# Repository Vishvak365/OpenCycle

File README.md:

# OpenCycle

An open-source GPS bike computer you print, solder and own.

- **Screen:** 2.4" IPS TFT, 240 × 320, 1200 nit (Newhaven, ST7789), auto-dimmed by an ambient-light sensor.
- **Radios:** ESP32-S3 (Wi-Fi, Bluetooth to the phone, native USB) + Ezurio BL652 for ANT+ and Bluetooth sensors + u-blox MAX-M10S GPS with a 12 mm ceramic patch.
- **Also:** BMP581 barometer, I²S amp and sealed speaker, 3 soft keys + 2 side buttons, USB-C charging.
- **Battery:** 1200 mAh LiPo, ~10–22 h riding (estimate, not measured).
- **Case:** 52 × 92.4 × 17 mm, FDM-printed, Garmin quarter-turn mount; standard, aero and rugged shells.
- **Parts:** ~$89 per unit, every part priced and linked (Mouser + Digi-Key).

Everything is generated from source: the enclosure (CadQuery), the board **and** its schematic (KiCad 7 through Python + Freerouting), the BOMs, the print files and the 3D viewer.

## Status (v0.2)

| Area | State |
|---|---|
| Enclosure | Done. Fit-checked against placeholders and against every real part on the routed board. Print-ready STLs in [`print/`](print/README.md). |
| PCB | Routed, 4 layers. **DRC 0 errors / 0 unconnected**, ERC 0 errors, schematic netlist = board netlist. Gerbers, BOM and CPL in [`pcb/fab/`](pcb/fab). |
| Parts | Complete BOM with prices, links and specs: [`docs/sourcing/bom-v0.2.md`](docs/sourcing/bom-v0.2.md). |
| UI | "Lucent" design language, 10 screens: [`docs/UI.md`](docs/UI.md). |
| Firmware | Not started. The owner is finishing the UI first. Plan: [`docs/FIRMWARE.md`](docs/FIRMWARE.md). |

> **Ready to order a first prototype run, not yet built.** Nothing has been soldered or powered up. Treat the first five boards as prototypes and read the "not verified" list in [`pcb/README.md`](pcb/README.md) (RF, battery lead polarity, JLCPCB part rotations) before you pay.

## Build one

Step-by-step guides are in [`instructions/`](instructions/README.md):

1. [Order the parts](instructions/01-order-parts.md)
2. [Order the PCBs](instructions/02-order-pcb.md)
3. [Print the case](instructions/03-print-case.md)
4. [Assemble the board](instructions/04-assemble-board.md)
5. [Bring it up](instructions/05-bring-up.md)
6. [Final assembly](instructions/06-final-assembly.md)
7. [Next steps](instructions/07-next-steps.md)

## The board

A time-lapse of the board being generated (placement, fan-out, routing, pours) is in [`docs/media/pcb_timelapse.mp4`](docs/media/pcb_timelapse.mp4).

## The interface

## What's here

| Path | What it is |
|---|---|
| `cad/` | Parametric enclosure (CadQuery). `params.py` holds every dimension; `check_fit.py` and `board_fit.py` check it. |
| `pcb/` | `design.py` (parts, nets, placement, rules) → board, schematic, fab files. Status in `pcb/README.md`. |
| `print/` | Print-oriented STLs, STEP files and the cover-lens outline. |
| `viewer/` | three.js pages: `index.html` (studio viewer with net explorer) and `product.html` (product page). The Lucent reference renderer is `viewer/ui/screens_color.js`. |
| `instructions/` | How to order, build and bring up a unit. |
| `docs/` | Hardware, PCB, CAD, UI, sourcing and decision docs. Start with [`docs/README.md`](docs/README.md). |
| `tools/` | `build_all.sh` rebuilds everything; exporters for meshes, print files, BOM and the time-lapse. |
| `AGENTS.md` | Where the truth lives and what not to break, for AI agents and new contributors. |

## Quick start

```bash
# view the product (the generated assets are committed)
python3 -m http.server -d viewer 8000     # open http://localhost:8000/product.html or /index.html

# rebuild everything (CadQuery, KiCad 7, Java for Freerouting; see docs/SETUP.md)
./tools/build_all.sh
```

## Licence

No licence file has been chosen yet; until one is added, all rights are reserved by the author. The Inter typeface in `viewer/ui/fonts/` is used under the SIL Open Font License (`OFL-Inter.txt`).

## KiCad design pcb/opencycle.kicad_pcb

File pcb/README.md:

# OpenCycle main board v0.2 — status

**Ready to order a first prototype run** (5 boards): routed, DRC clean, schematic generated and netlist-matched, parts sourced, fab files exported. **Not yet built or tested** — treat the first run as a prototype and follow [`../instructions/05-bring-up.md`](../instructions/05-bring-up.md).

| What | Where |
|---|---|
| Board | `opencycle.kicad_pcb` (+ `.kicad_pro`, `.kicad_dru`, `fp-lib-table`, `sym-lib-table`: opens in KiCad 7+) |
| Schematic | `opencycle.kicad_sch`, PDF in `fab/opencycle_schematic.pdf` |
| Gerbers + drill | `fab/opencycle_v0.2_gerbers.zip` (upload to JLCPCB as-is) |
| Assembly | `fab/bom_jlcpcb.csv`, `fab/cpl_jlcpcb.csv`, `fab/assembly_front.pdf`, `fab/assembly_back.pdf` |
| Order list | `fab/bom_distributors.csv` and [`../docs/sourcing/bom-v0.2.md`](../docs/sourcing/bom-v0.2.md) |
| Checks | `drc_report.txt`, `erc_report.txt`, `check_place.py`, `check_netlist.py`, `../cad/board_fit.py` |

Everything is generated from `design.py` — do not hand-edit the board and then regenerate, you will lose the edit. If you do route by hand in KiCad, stop using the pipeline for that board and say so in `docs/DECISIONS.md`.

## Verified

- Pinouts of every IC/module against the manufacturer datasheet (see the header of `design.py` for the list and `docs/sourcing/part-specs.md` for details). Two errors in earlier notes were found and fixed: the BMP581 pin order and MAX-M10S pin 15.
- Land patterns drawn from datasheet drawings for the BMP581 and the Taoglas 12 mm patch; all other footprints from the KiCad 7 library.
- Mechanical fit of every real part (datasheet heights) against the enclosure, display, folded FFC, battery and speaker.
- DRC 0 errors / 0 unconnected; ERC 0 errors; schematic netlist == board netlist.

## Not verified (look at these before ordering / during bring-up)

1. **RF performance** of all three antennas (GPS patch ground is 46 mm wide and cut by the radio keep-outs; Taoglas characterised it on 50 × 50 mm). Expect to tune firmware (GPS LNA gain) and possibly move to a pin-fed patch later.
2. **Battery polarity** of the Adafruit lead vs. J2 (pin 1 −, pin 2 +). Q2 blocks a reversed cell, but measure before plugging in.
3. **JLCPCB rotation offsets** in `cpl_jlcpcb.csv` — JLC's preview shows each part; fix any that are rotated (common for SOT-23, QFN and connectors) in their tool before paying.
4. **RF_IN impedance**: 0.2 mm on the 1.0 mm JLC04101H-3313 stack-up is close to 50 Ω; confirm with the JLC impedance calculator or ask for impedance control.
5. **Backlight brightness** with 33 Ω ballasts: ≤ 45 mA per LED in the worst case (4.2 V, Vf 2.7 V), ~21 mA typical, so full brightness is only reached on a full battery. Don't lower the ballasts unless firmware caps the PWM duty from VBAT_SENSE: at 22 Ω the worst case is 68 mA per LED, above the 50 mA per-LED limit.
6. **Charging while running:** there is no USB power path — the system always runs from VBAT and the MCP73831 charges the cell and feeds the load in parallel (the same approach as Adafruit Feather boards). While the device is on and plugged in, the charger may not terminate (it holds 4.20 V). Fine for a few hours of charging; a power-path charger (e.g. BQ24072) is the v0.3 upgrade if this matters.
7. **Firmware**: nothing is written yet; the pin map is in `docs/HARDWARE.md`.

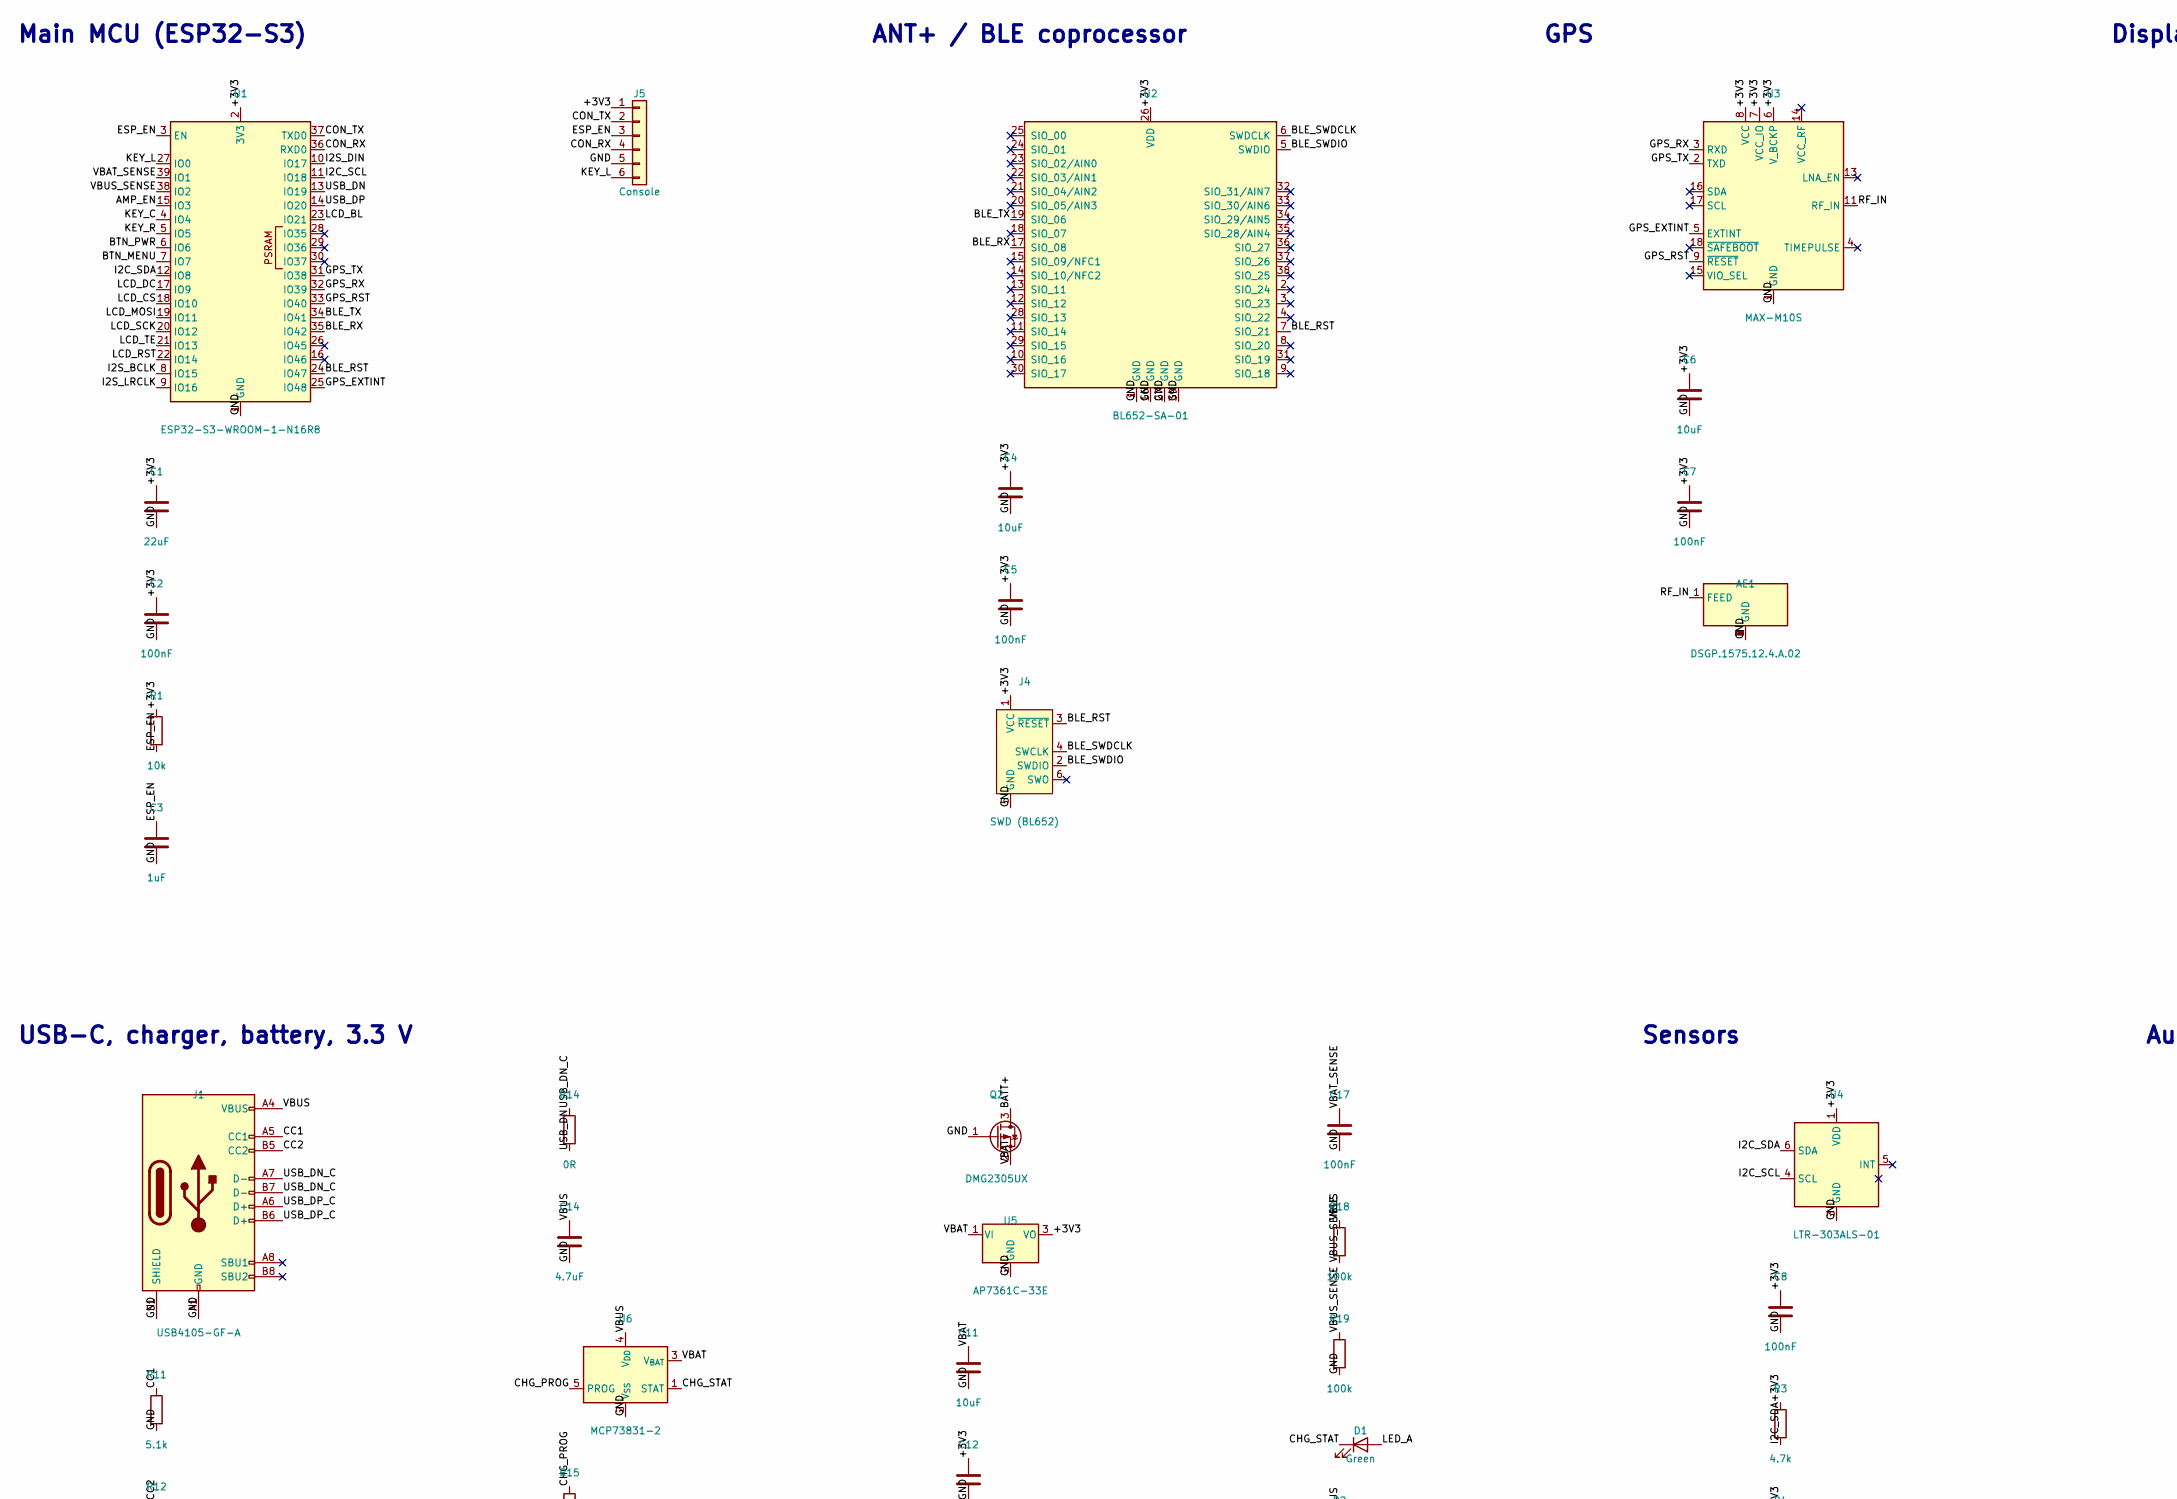
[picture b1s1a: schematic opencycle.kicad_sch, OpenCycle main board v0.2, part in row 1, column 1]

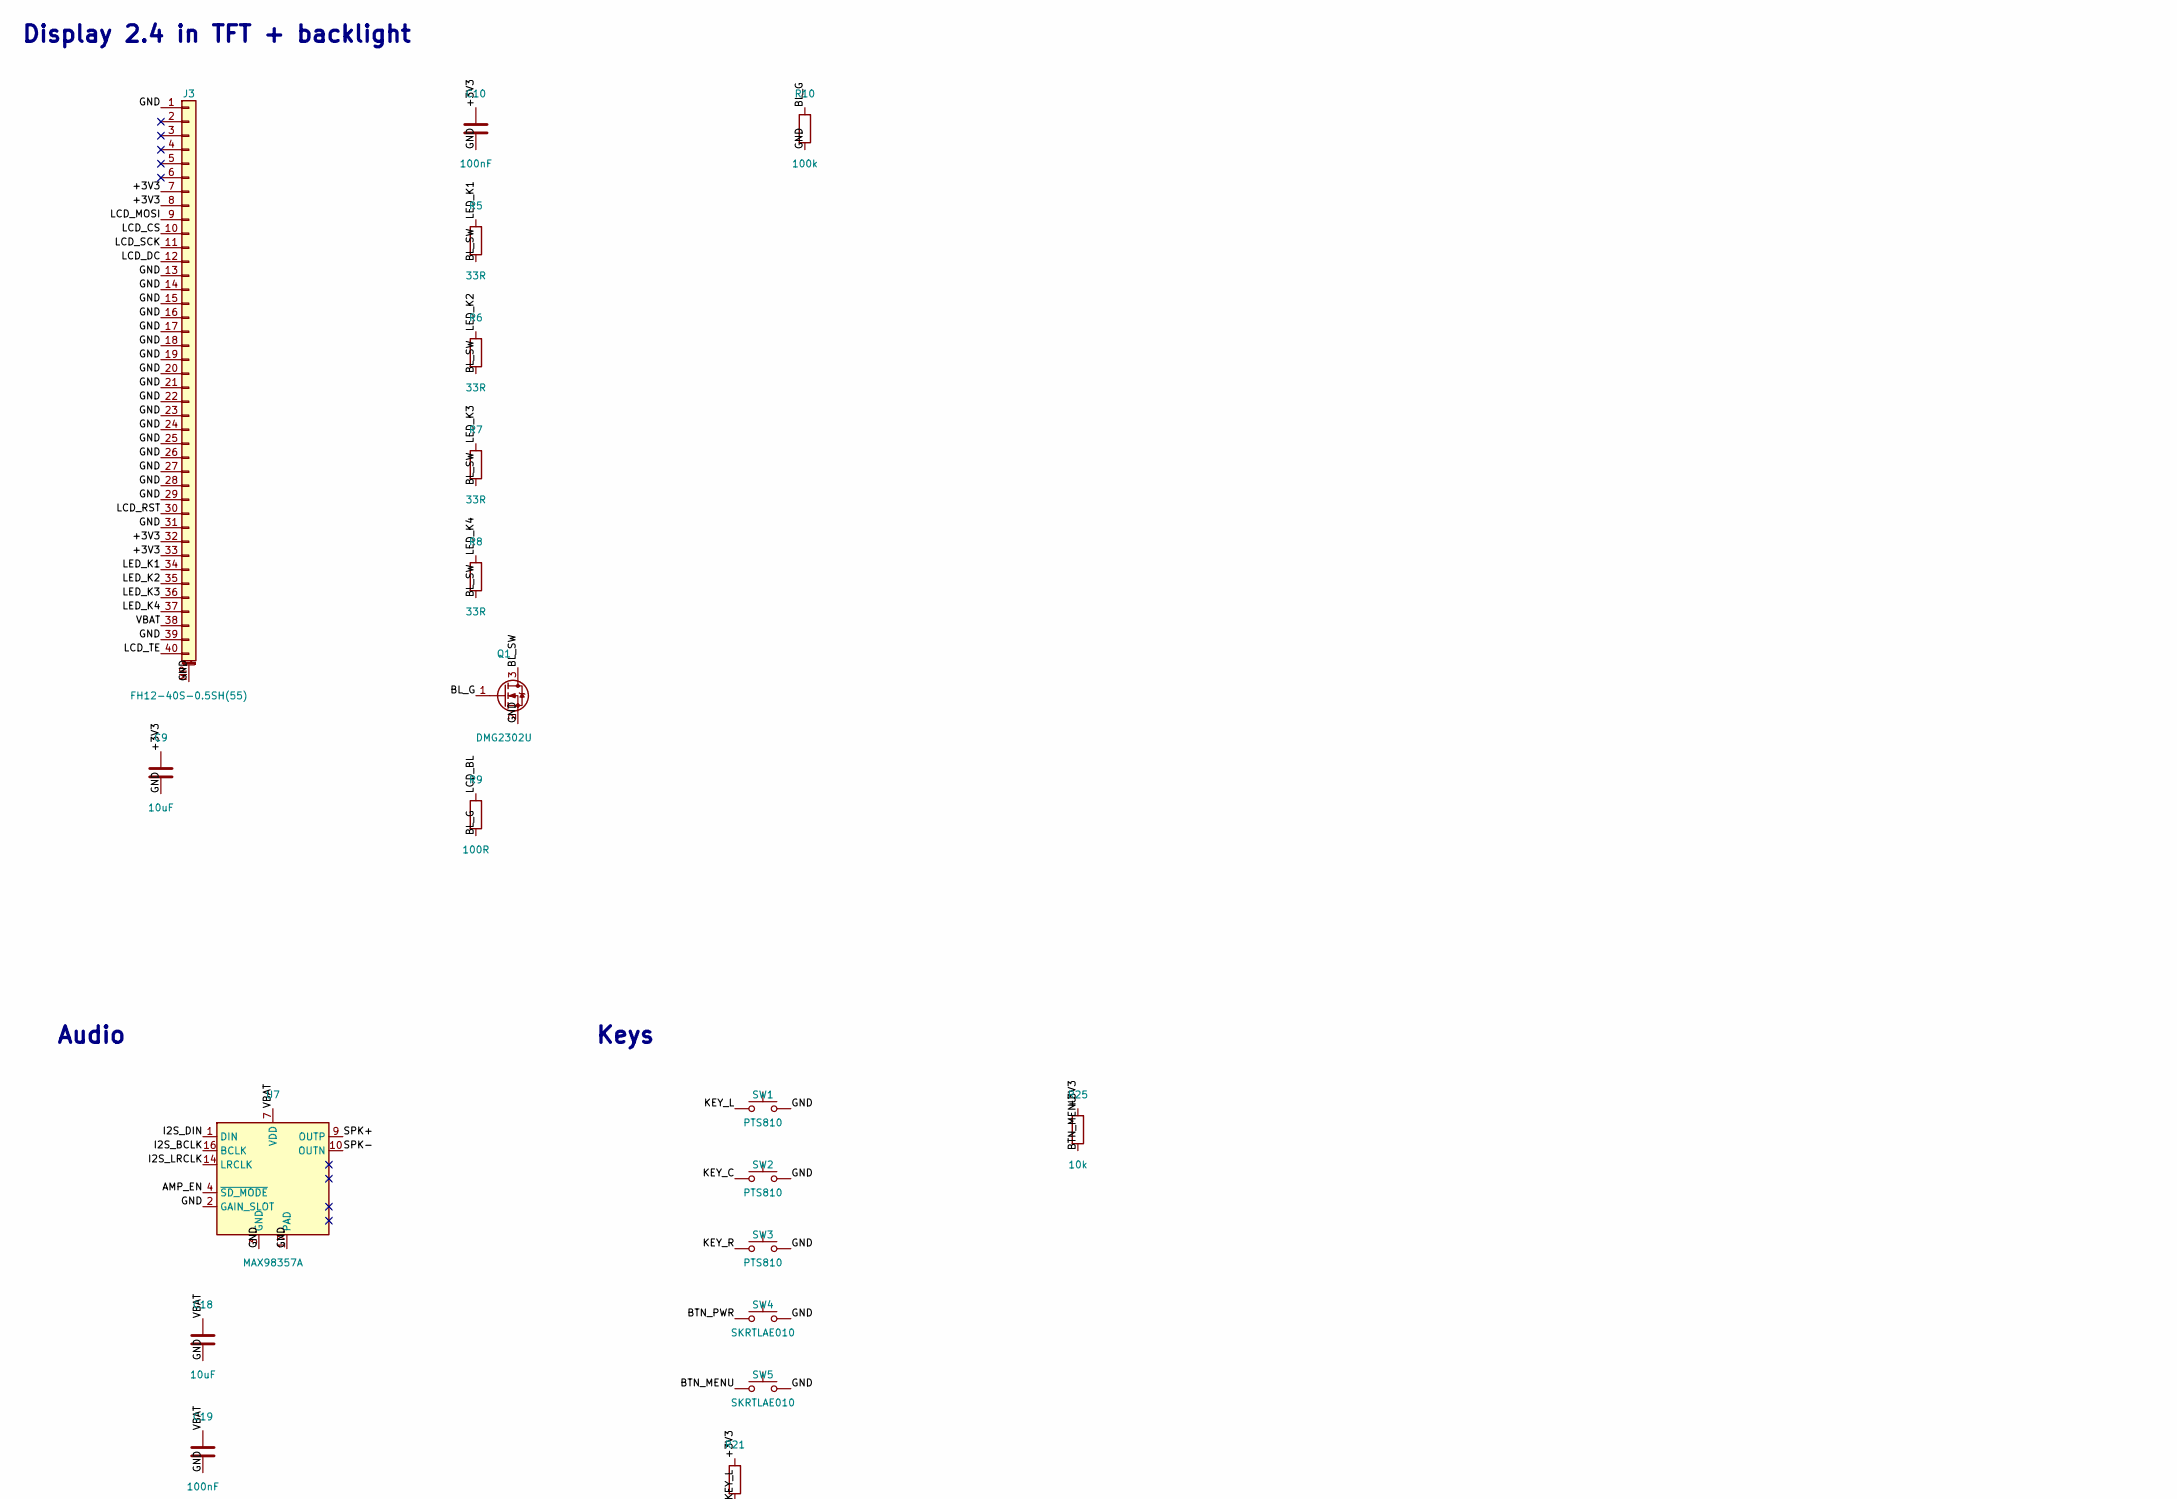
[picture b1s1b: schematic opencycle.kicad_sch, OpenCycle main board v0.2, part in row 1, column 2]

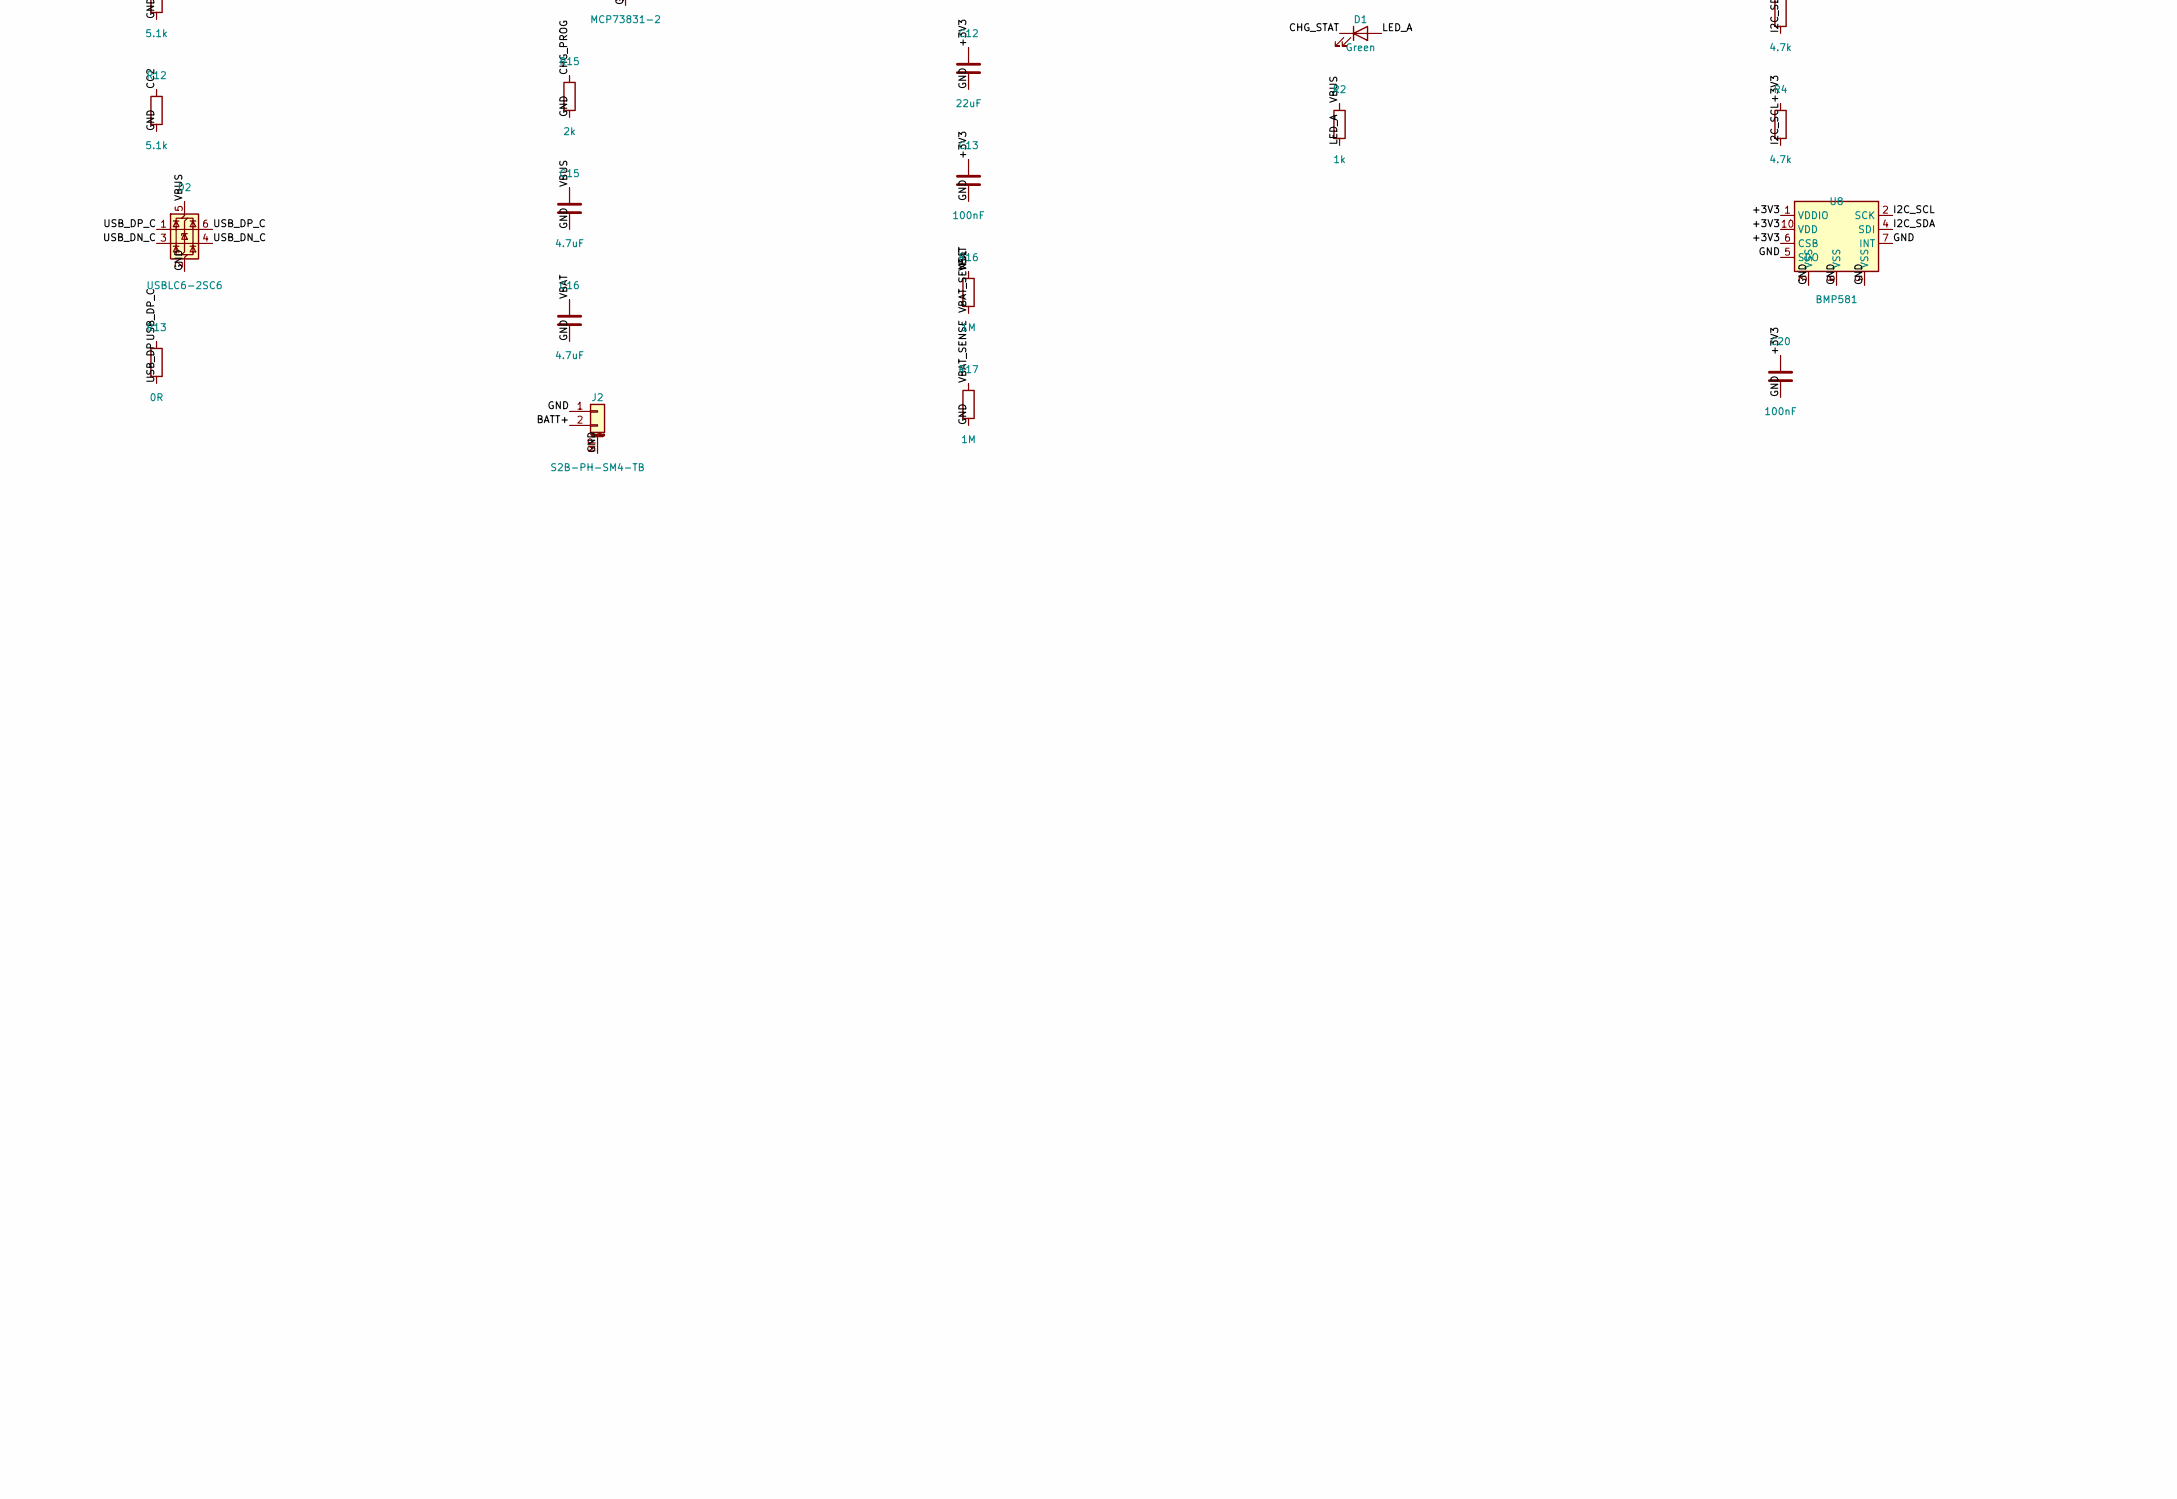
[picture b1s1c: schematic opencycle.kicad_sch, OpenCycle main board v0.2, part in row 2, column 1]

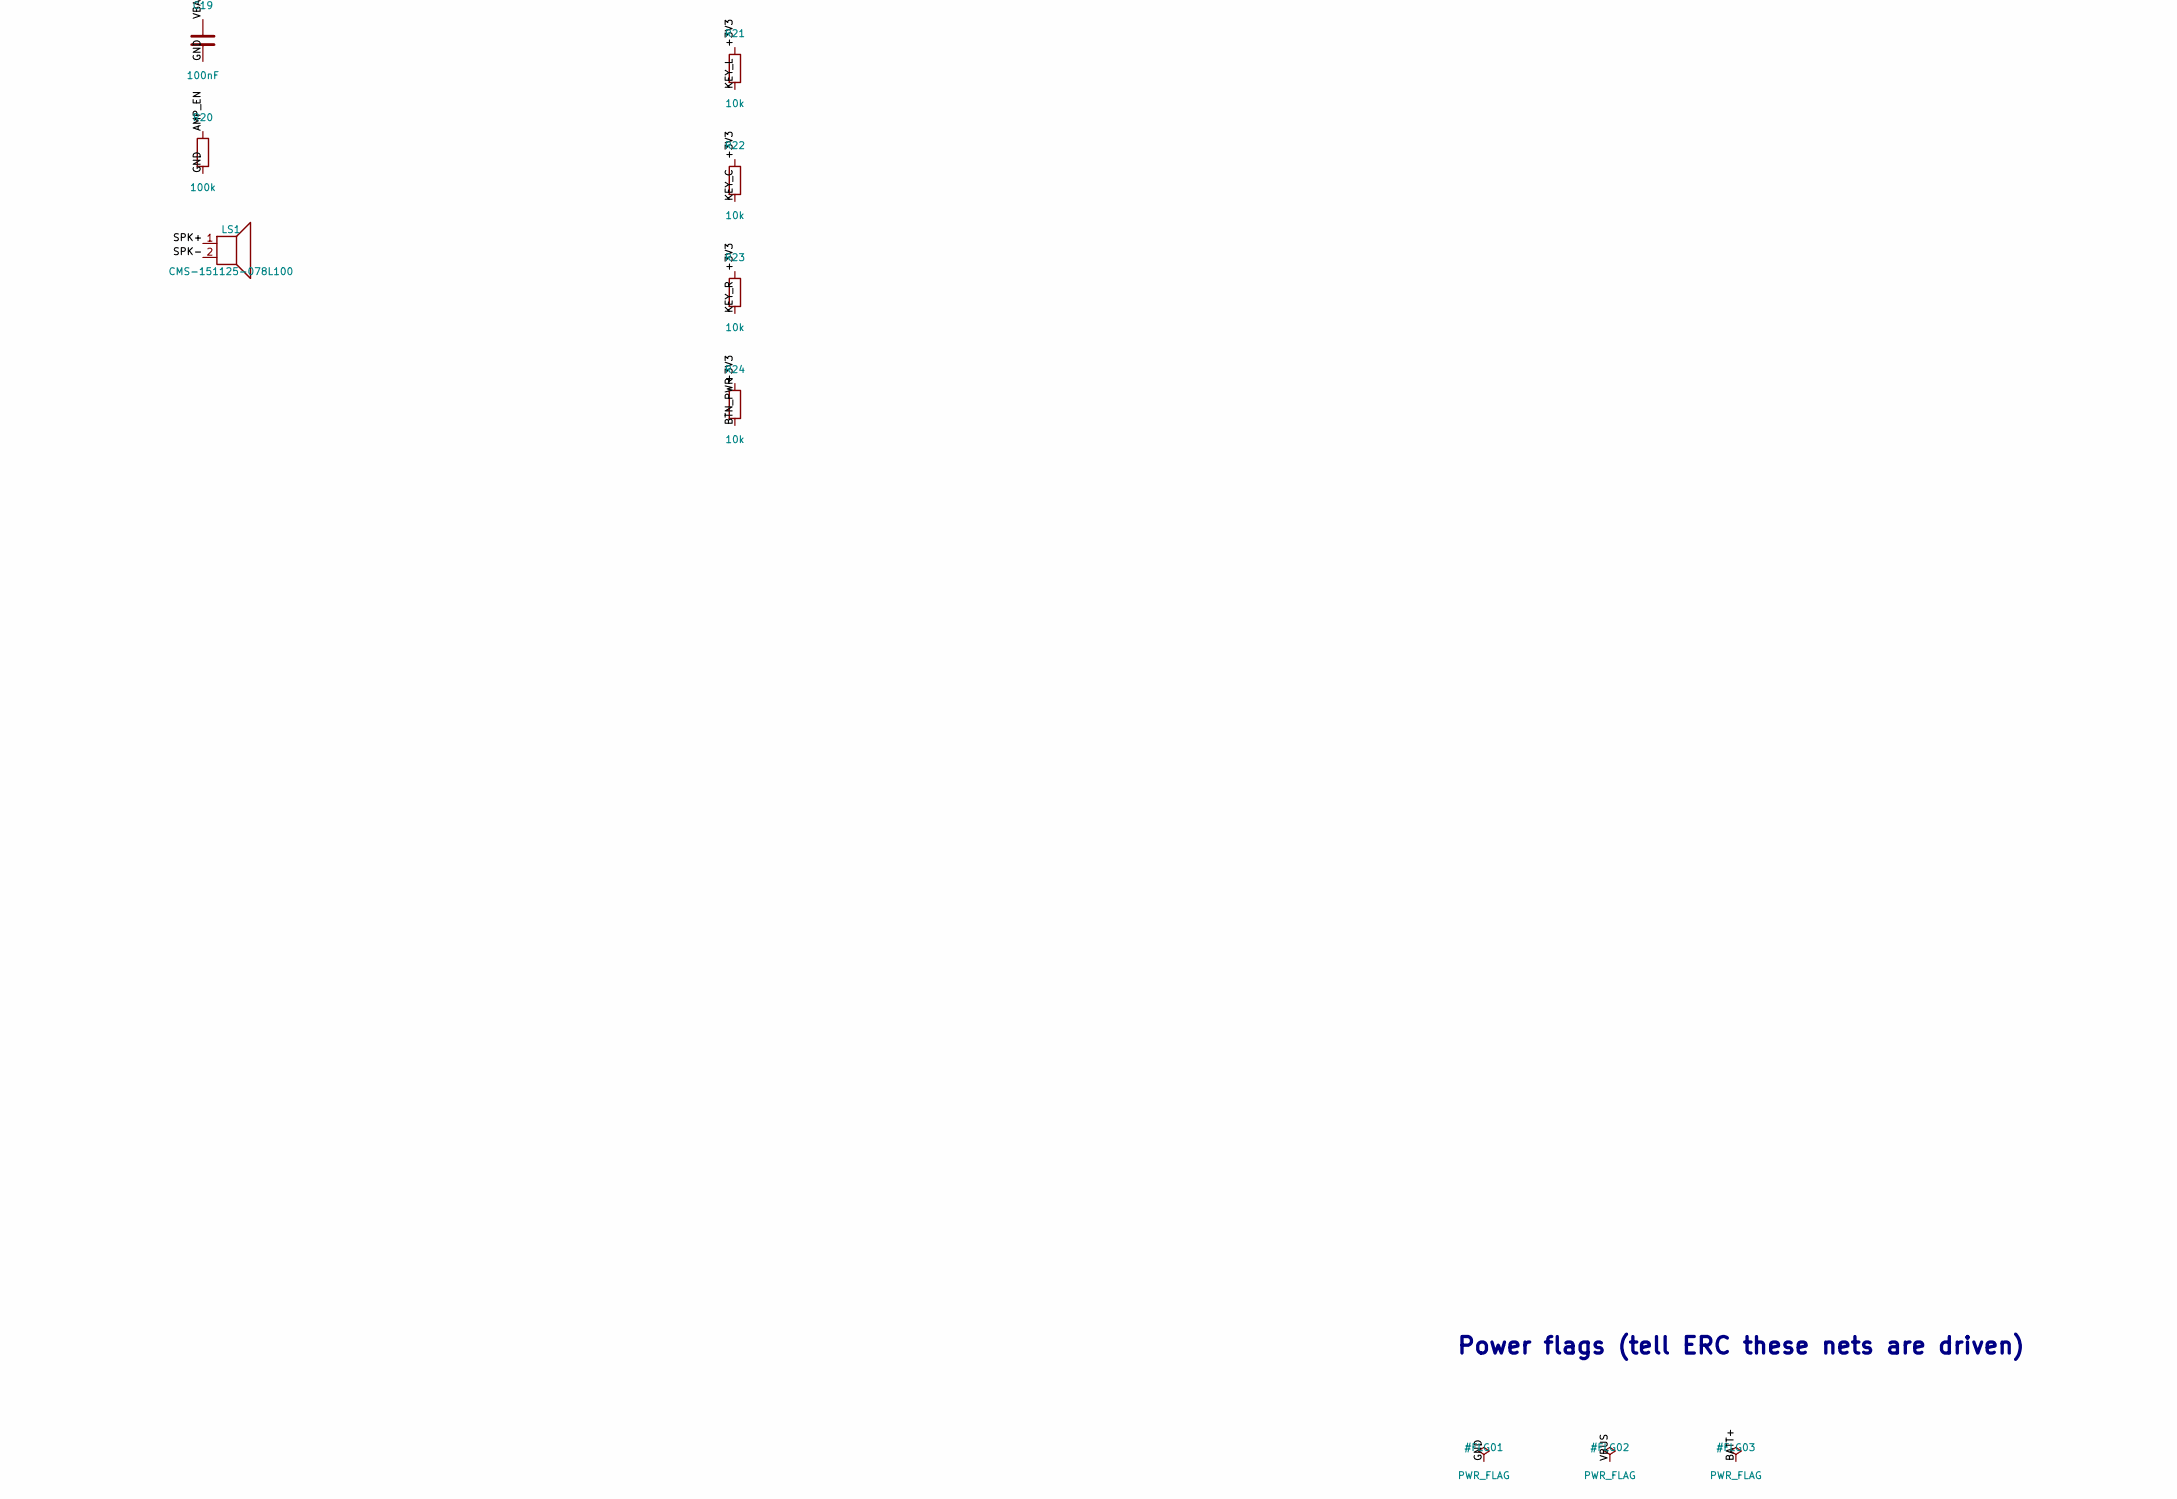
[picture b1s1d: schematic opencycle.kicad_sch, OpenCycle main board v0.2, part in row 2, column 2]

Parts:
AE1: DSGP.1575.12.4.A.02; Taoglas_DSGP.1575.12.4.A.02_12x12mm; MPN DSGP.1575.12.4.A.02
C1, C12: 22uF; C_0805_2012Metric; MPN CL21A226MAQNNNE
C2, C5, C7, C8, C10, C13, C17, C19, C20: 100nF; C_0402_1005Metric; MPN CL05B104KO5NNNC
C3: 1uF; C_0402_1005Metric; MPN CL05A105KO5NNNC
C4, C6, C9, C11, C18: 10uF; C_0603_1608Metric; MPN CL10A106KP8NNNC
C14, C15, C16: 4.7uF; C_0603_1608Metric; MPN CL10A475KO8NNNC
D1: Green; LED_0603_1608Metric; MPN LTST-C191KGKT
D2: USBLC6-2SC6; SOT-23-6; MPN USBLC6-2SC6
J1: USB4105-GF-A; USB_C_Receptacle_GCT_USB4105-xx-A_16P_TopMnt_Horizontal; MPN USB4105-GF-A
J2: S2B-PH-SM4-TB; JST_PH_S2B-PH-SM4-TB_1x02-1MP_P2.00mm_Horizontal; MPN S2B-PH-SM4-TB(LF)(SN)
J3: FH12-40S-0.5SH(55); Hirose_FH12-40S-0.5SH_1x40-1MP_P0.50mm_Horizontal; MPN FH12-40S-0.5SH(55)
J4: SWD (BL652); Tag-Connect_TC2030-IDC-NL_2x03_P1.27mm_Vertical
J5: Console; Tag-Connect_TC2030-IDC-NL_2x03_P1.27mm_Vertical
LS1: CMS-151125-078L100; SpeakerPads_2.6mm; MPN CMS-151125-078L100
Q1: DMG2302U; SOT-23; MPN DMG2302UK-7
Q2: DMG2305UX; SOT-23; MPN DMG2305UX-7
R1, R21, R22, R23, R24, R25: 10k; R_0402_1005Metric; MPN RC0402FR-0710KL
R2: 1k; R_0402_1005Metric; MPN RC0402FR-071KL
R3, R4: 4.7k; R_0402_1005Metric; MPN RC0402FR-074K7L
R5, R6, R7, R8: 33R; R_0603_1608Metric; MPN RC0603FR-0733RL
R9: 100R; R_0402_1005Metric; MPN RC0402FR-07100RL
R10, R18, R19, R20: 100k; R_0402_1005Metric; MPN RC0402FR-07100KL
R11, R12: 5.1k; R_0402_1005Metric; MPN RC0402FR-075K1L
R13, R14: 0R; R_0402_1005Metric; MPN RC0402JR-070RL
R15: 2k; R_0402_1005Metric; MPN RC0402FR-072KL
R16, R17: 1M; R_0402_1005Metric; MPN RC0402FR-071ML
SW1, SW2, SW3: PTS810; SW_SPST_PTS810; MPN PTS810 SJM 250 SMTR LFS
SW4, SW5: SKRTLAE010; SW_Push_1P1T-MP_NO_Horizontal_Alps_SKRTLAE010; MPN SKRTLAE010
U1: ESP32-S3-WROOM-1-N16R8; ESP32-S3-WROOM-1; MPN ESP32-S3-WROOM-1-N16R8
U2: BL652-SA-01; Laird_BL652; MPN BL652-SA-01-T/R
U3: MAX-M10S; ublox_MAX; MPN MAX-M10S-00B
U4: LTR-303ALS-01; Lite-On_LTR-303ALS-01; MPN LTR-303ALS-01
U5: AP7361C-33E; SOT-223-3_TabPin2; MPN AP7361C-33E-13
U6: MCP73831-2; SOT-23-5; MPN MCP73831T-2ACI/OT
U7: MAX98357A; TQFN-16-1EP_3x3mm_P0.5mm_EP1.23x1.23mm; MPN MAX98357AETE+T
U8: BMP581; Bosch_LGA-10_2x2mm_P0.5mm_BMP581; MPN BMP581

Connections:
+3V3: C1.1, C2.1, C4.1, C5.1, C6.1, C7.1, C8.1, C9.1, C10.1, C12.1, C13.1, C20.1, J3.7, J3.8, J3.32, J3.33, J4.1 (VCC), J5.1, R1.1, R3.1, R4.1, R21.1, R22.1, R23.1, R24.1, R25.1, U1.2 (3V3), U2.26 (VDD), U3.6 (V_BCKP), U3.7 (VCC_IO), U3.8 (VCC), U4.1 (VDD), U5.3 (VO), U8.1 (VDDIO), U8.6 (CSB), U8.10 (VDD)
AMP_EN: R20.1, U1.15 (IO3), U7.4 (~SD_MODE)
BATT+: J2.2, Q2.3 (D)
BLE_RST: J4.3 (~RESET), U1.24 (IO47), U2.7 (SIO_21)
BLE_RX: U1.35 (IO42), U2.17 (SIO_08)
BLE_SWDCLK: J4.4 (SWCLK), U2.6 (SWDCLK)
BLE_SWDIO: J4.2 (SWDIO), U2.5 (SWDIO)
BLE_TX: U1.34 (IO41), U2.19 (SIO_06)
BL_G: Q1.1 (G), R9.2, R10.1
BL_SW: Q1.3 (D), R5.2, R6.2, R7.2, R8.2
BTN_MENU: R25.2, SW5.1, U1.7 (IO7)
BTN_PWR: R24.2, SW4.1, U1.6 (IO6)
CC1: J1.A5 (CC1), R11.1
CC2: J1.B5 (CC2), R12.1
CHG_PROG: R15.1, U6.5 (PROG)
CHG_STAT: D1.1 (K), U6.1 (STAT)
CON_RX: J5.4, U1.36 (RXD0)
CON_TX: J5.2, U1.37 (TXD0)
ESP_EN: C3.1, J5.3, R1.2, U1.3 (EN)
GND: AE1.2 (GND), AE1.3 (GND), AE1.4 (GND), AE1.5 (GND), AE1.6 (GND), AE1.7 (GND), AE1.8 (GND), AE1.9 (GND), C1.2, C2.2, C3.2, C4.2, C5.2, C6.2, C7.2, C8.2, C9.2, C10.2, C11.2, C12.2, C13.2, C14.2, C15.2, C16.2, C17.2, C18.2, C19.2, C20.2, D2.2 (GND), J1.A1 (GND), J1.A12 (GND), J1.B1 (GND), J1.B12 (GND), J1.S1 (SHIELD), J2.1, J2.MP (MountPin), J3.1, J3.13, J3.14, J3.15, J3.16, J3.17, J3.18, J3.19, J3.20, J3.21, J3.22, J3.23, J3.24, J3.25, J3.26, J3.27, J3.28, J3.29, J3.31, J3.39, J3.MP (MountPin), J4.5 (GND), J5.5, Q1.2 (S), Q2.1 (G), R10.2, R11.2, R12.2, R15.2, R17.2, R19.2, R20.2, SW1.2, SW2.2, SW3.2, SW4.2, SW4.MP, SW5.2, SW5.MP, U1.1 (GND), U1.40 (GND), U1.41 (GND), U2.1 (GND), U2.16 (GND), U2.27 (GND), U2.39 (GND), U3.1 (GND), U3.10 (GND), U3.12 (GND), U4.3 (GND), U5.2 (GND), U6.2 (V_{SS}), U7.2 (GAIN_SLOT), U7.3 (GND), U7.11 (GND), U7.15 (GND), U7.17 (PAD), U8.3 (VSS), U8.5 (SDO), U8.7 (INT), U8.8 (VSS), U8.9 (VSS); also elsewhere on the board
GPS_EXTINT: U1.25 (IO48), U3.5 (EXTINT)
GPS_RST: U1.33 (IO40), U3.9 (~RESET)
GPS_RX: U1.32 (IO39), U3.3 (RXD)
GPS_TX: U1.31 (IO38), U3.2 (TXD)
I2C_SCL: R4.2, U1.11 (IO18), U4.4 (SCL), U8.2 (SCK)
I2C_SDA: R3.2, U1.12 (IO8), U4.6 (SDA), U8.4 (SDI)
I2S_BCLK: U1.8 (IO15), U7.16 (BCLK)
I2S_DIN: U1.10 (IO17), U7.1 (DIN)
I2S_LRCLK: U1.9 (IO16), U7.14 (LRCLK)
KEY_C: R22.2, SW2.1, U1.4 (IO4)
KEY_L: J5.6, R21.2, SW1.1, U1.27 (IO0)
KEY_R: R23.2, SW3.1, U1.5 (IO5)
LCD_BL: R9.1, U1.23 (IO21)
LCD_CS: J3.10, U1.18 (IO10)
LCD_DC: J3.12, U1.17 (IO9)
LCD_MOSI: J3.9, U1.19 (IO11)
LCD_RST: J3.30, U1.22 (IO14)
LCD_SCK: J3.11, U1.20 (IO12)
LCD_TE: J3.40, U1.21 (IO13)
LED_A: D1.2 (A), R2.2
LED_K1: J3.34, R5.1
LED_K2: J3.35, R6.1
LED_K3: J3.36, R7.1
LED_K4: J3.37, R8.1
RF_IN: AE1.1 (FEED), U3.11 (RF_IN)
SPK+: LS1.1, U7.9 (OUTP)
SPK-: LS1.2, U7.10 (OUTN)
USB_DN: R14.2, U1.13 (IO19)
USB_DN_C: D2.3 (I/O2), D2.4 (I/O2), J1.A7 (D-), J1.B7 (D-), R14.1
USB_DP: R13.2, U1.14 (IO20)
USB_DP_C: D2.1 (I/O1), D2.6 (I/O1), J1.A6 (D+), J1.B6 (D+), R13.1
VBAT: C11.1, C16.1, C18.1, C19.1, J3.38, Q2.2 (S), R16.1, U5.1 (VI), U6.3 (V_{BAT}), U7.7 (VDD), U7.8 (VDD)
VBAT_SENSE: C17.1, R16.2, R17.1, U1.39 (IO1)
VBUS: C14.1, C15.1, D2.5 (VBUS), J1.A4 (VBUS), J1.A9 (VBUS), J1.B4 (VBUS), J1.B9 (VBUS), R2.1, R18.1, U6.4 (V_{DD})
VBUS_SENSE: R18.2, R19.1, U1.38 (IO2)

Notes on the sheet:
Main MCU (ESP32-S3)
ANT+ / BLE coprocessor
GPS
Display 2.4 in TFT + backlight
USB-C, charger, battery, 3.3 V
Sensors
Audio
Keys
Power flags (tell ERC these nets are driven)
